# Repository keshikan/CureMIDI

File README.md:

# USB-MIDI Interface (2IN/2OUT) for STM32 "CureMIDI"

## Overview

This repository shows STM32F0 (ARM Cortex-M0) based USB-MIDI Interface.
It has 2 MIDI-IN and 2 MIDI-OUT, and is USB MIDI class-compliant.

The USB-MIDI Class Driver is based on [mimuz-tuch](https://github.com/mimuz/mimuz-tuch) project (c) [D.F.Mac. @TripArts Music](https://github.com/tadfmac).

STM32F0を使用した、USB-MIDIインターフェースです。INを2系統、OUTを2系統実装しています。USB MIDI Classに対応するシステム(Windows, iOS, Android, etc.)に対し、ドライバレスでMIDI入出力ポートを追加できます。

USB MIDI Classドライバは、[D.F.Mac. @TripArts Music](https://github.com/tadfmac)氏作成の[ドライバ](https://github.com/mimuz/mimuz-tuch/tree/master/STM32)を基に、一部改造を加えています。

## Specifications

* USB MIDI class-compliant
* MIDI port: 2IN/2OUT
* MIDI buffer size: 512B/1port

## Building Information

### Making hardware

See [Schematic](./hardware/schematic.pdf), [KiCad Source](./hardware/kicad_source).

### Building software

Install [SW4STM32](http://www.openstm32.org/HomePage)(need registration), import [Project files](./software/SW4STM32_project/), and build.

## File Location

* [Binary file for STM32F042](./software/bin/)
* [STM32CubeMX Project file](./software/SW4STM32_project/CureMIDI_IF.ioc)
* [Source codes and project files (System WorkBench for STM32)](./software/SW4STM32_project/)
* [Schematic](./hardware/schematic.pdf)

## NOTICE

### VID/PID

Vendor ID(VID) and Product ID(PID) in <usbd_desc.c> should be unique pair for each USB devices.
Default VID 0x1209 and PID 0x0001 is experimental IDs from [http://pid.codes](http://pid.codes) .When distributing or selling, you must get your own IDs, and change to your own IDs in order to avoid conflicting to other USB devices.

USBのVendor ID(VID)とProduct ID(PID)は、<usbd_desc.c>内に記述します。
デフォルトのVID(0x1209)/PID(0x0001)ペアは、[http://pid.codes](http://pid.codes)で定められている実験用IDです。そのため、本機器を配布したり販売したりする場合には、別途固有のIDペアを取得し、書き換えてご使用下さい。

## References

### MIDI specification

* [The Complete MIDI 1.0 Detailed Specification](https://www.midi.org/specifications/item/the-midi-1-0-specification) ([MIDI Association](https://www.midi.org/))
* [MIDI1.0規格書](http://amei.or.jp/midistandardcommittee/MIDI1.0.pdf) ([AMEI](http://amei.or.jp/))
* [MIDIの学習](http://www1.plala.or.jp/yuuto/midi/index.html) ([Laboratory "U"](http://www1.plala.or.jp/yuuto/top.html))

### USB-MIDI technical information

* [Universal Serial Bus Device Class Definition for MIDI Devices](http://www.usb.org/developers/docs/devclass_docs/midi10.pdf)
* [USBおよびUSB MIDIについて調べる](http://picmidi.seesaa.net/article/150728556.html) ([PICでMIDI！](http://picmidi.seesaa.net/))

## Copyrights

* USB MIDI Class Driver by [D.F.Mac. @TripArts Music](http://ta-music.strikingly.com/)
* STM32 CubeF0 by [STMicroelectronics](https://www.st.com/en/embedded-software/stm32cubef0.html)

## Author

(c) 2018 Keshikan ( [Website](http://www.keshikan.net/),  [Twitter](https://twitter.com/keshinomi_88pro) )

## License

* USB MIDI Class Driver: [CC BY 4.0](https://creativecommons.org/licenses/by/4.0/)
* STM32 CubeF0: BSD-3-Clause based.
* Other Codes, Hardware, Schematic: [GPLv3](https://www.gnu.org/licenses/gpl-3.0.html)

See also [LICENSE.md](./LICENSE.md)

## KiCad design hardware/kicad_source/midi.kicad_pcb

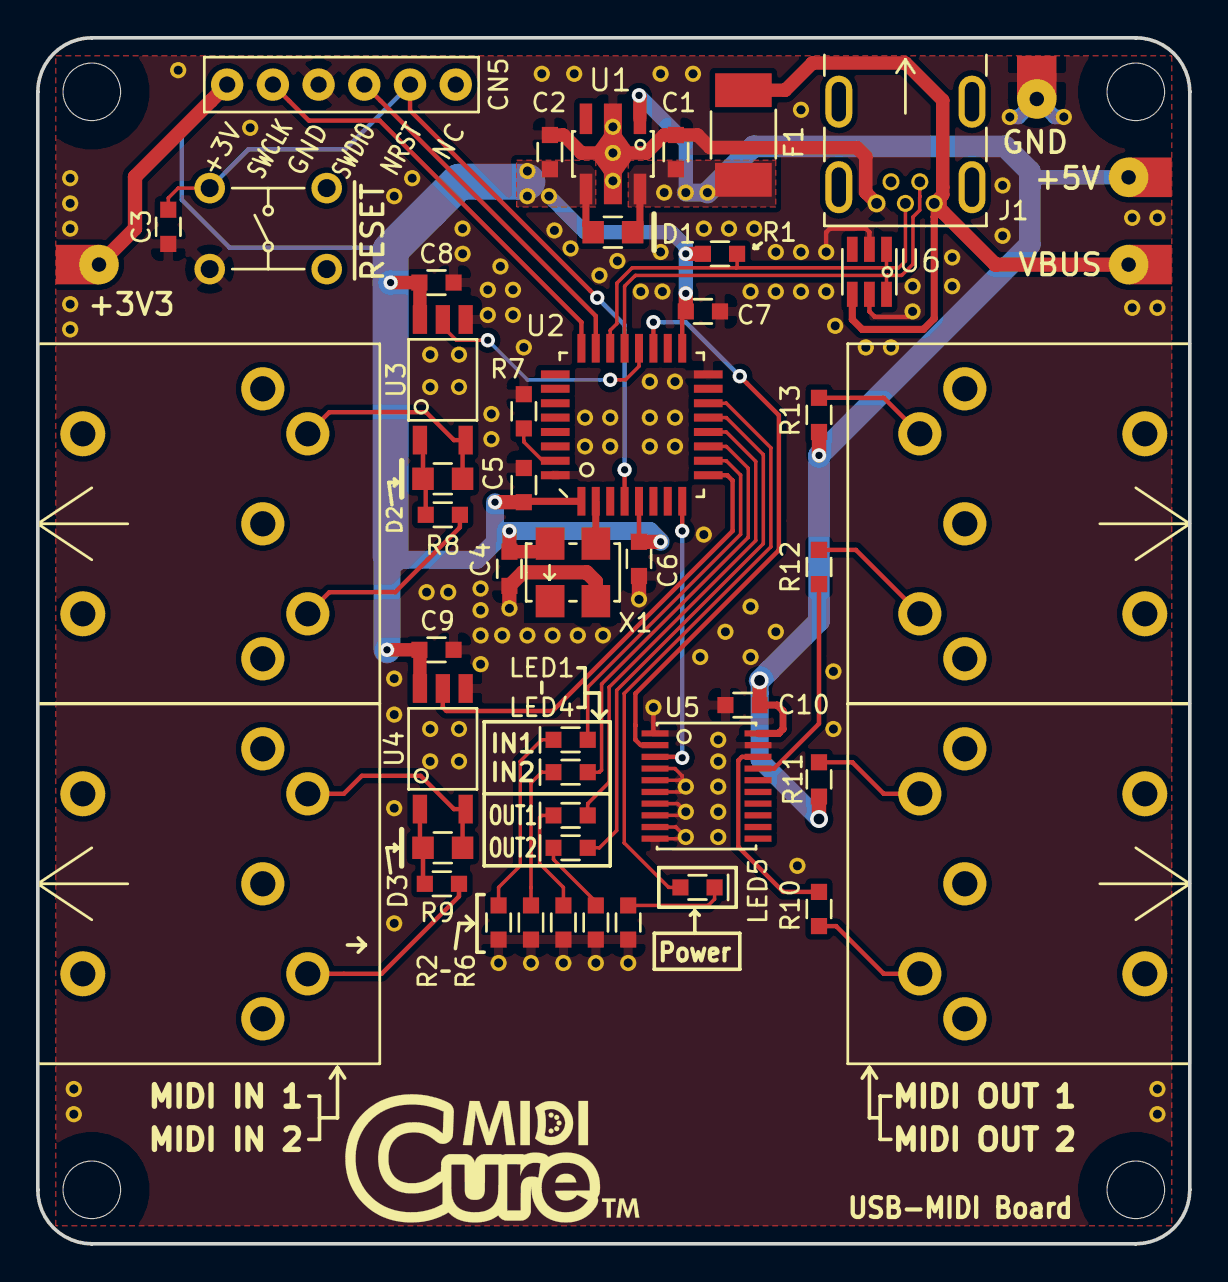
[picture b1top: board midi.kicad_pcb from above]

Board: 2 copper layers, 64.0 x 67.0 mm, 50 parts (0 on the bottom side), 37 nets.

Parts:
C1: 0.33μF; SMD_0603(1608)
C2: 2.2μF; SMD_0603(1608)
C3, C4, C5, C6, C7, C8, C9, C10: 0.1μF; SMD_0603(1608)
CN1, CN2, CN3, CN4: DIN_5; DIN_5P_MIDI
CN5: CONN_01X06; CONN_DIP_6Pin
D1: D_Schottky_Small; SMD_0805(2012)_polar
D2, D3: D_Small; SMD_0805(2012)_polar
F1: PolySW 0.35A; miniSMDC030F
J1: USB_OTG_ORIG; USB_miniB_MUSB-5BF01AS
LED1, LED2, LED3, LED4, LED5: Led_Small; SMD_0603(1608)_polar
P1: VBUS; CHK_Terminal_TH
P2: 5V; CHK_Terminal_TH
P3: CHK_GND; CHK_Terminal_TH
P4: 3V; CHK_Terminal_TH
R1: 4.7k; SMD_0603(1608)
R2, R3, R4, R5, R6: 750; SMD_0603(1608)
R7: 10k; SMD_0603(1608)
R8, R9, R10, R11, R12, R13: 220; SMD_0603(1608)
SW1: SW_PUSH_SMALL_H; Tactile_Switches_2by2
U1: NJM2884U1; SOT-89-5
U2: STM32F042K6Tx; LQFP32_7x7_STM32
U3, U4: TLP2361; 11-4L1S(TLP2361)
U5: 74VHCV541FT; TSSOP20B
U6: ESDA6V1BC6; SOT23-6L
X1: SG5032CAN 8MHz; SG5032

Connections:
+3V3: C2.1, C4.1, C5.1, C6.1, C7.1, C8.1, C9.1, CN5.1, D1.2, P4.1, R1.2, U1.VO, U2.1, U2.5, U2.17, U3.6, U4.6, X1.4
+5V: C1.1, C10.1, D1.1, F1.1, P2.1, R11.1, R13.1, U1.CTR, U1.VI, U5.20
GNDD: C1.2, C2.2, C3.2, C4.2, C5.2, C6.2, C7.2, C8.2, C9.2, C10.2, CN5.3, J1.5, P3.1, R2.1, R3.1, R4.1, R5.1, R6.1, R7.1, SW1.1, U1.GND, U2.16, U2.32, U3.4, U4.4, U5.1, U5.4, U5.5, U5.6, U5.7, U5.8, U5.9, U5.10, U5.19, U6.2, U6.5, X1.2
MIDI_IN_1: U2.20, U3.5
MIDI_IN_2: U2.9, U4.5
MIDI_OUT_1: U2.19, U5.2
MIDI_OUT_2: U2.8, U5.3
NRST: C3.1, CN5.5, SW1.2, U2.4
unnamed: CN1.4, R8.1
unnamed: CN1.5, D2.2, U3.3
unnamed: CN2.4, R9.1
unnamed: CN2.5, D3.2, U4.3
unnamed: CN3.4, R11.2
unnamed: CN3.5, R10.2
unnamed: CN4.4, R13.2
unnamed: CN4.5, R12.2
unnamed: D2.1, R8.2, U3.1
unnamed: D3.1, R9.2, U4.1
unnamed: LED1.1, R2.2
unnamed: LED1.2, U2.10
unnamed: LED2.1, R3.2
unnamed: LED2.2, U2.11
unnamed: LED3.1, R4.2
unnamed: LED3.2, U2.12
unnamed: LED4.1, R5.2
unnamed: LED4.2, U2.13
unnamed: LED5.1, R6.2
unnamed: LED5.2, U2.14
unnamed: R7.2, U2.31
unnamed: R10.1, U5.18
unnamed: R12.1, U5.17
unnamed: U2.2, X1.3
SWCLK: CN5.2, U2.24
SWDIO: CN5.4, U2.23
USBD_N: J1.2, U2.21, U6.6
USBD_P: J1.3, R1.1, U2.22, U6.1
VBUS: F1.2, J1.1, P1.1, U6.4

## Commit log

2019-06-14 Added KiCad source files
